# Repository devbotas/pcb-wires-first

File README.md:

# The Problem

Wireless IoT sucks.

It's unreliable and breaks all the time. There's not such thing as reliable, maintenance-free, wireless IoT.

If it runs on batteries - that's even worse.

Another problem - central IoT hubs. If those break, lose connection, decides to reboot ar whatever - my smart house immediatelly becomes non-functional.

# The Solution

Put the analog wires first! So that light switches continue to operate even if smart features decide to stop working.

# The Boards

## Gateway

This is a simple carrier board for WizNET W55RP20 development module. It cannot do much by itself - maybe blink some LEDs. Real functionality (and also power) should come from the JST PH headers.

Can be mounted on M or L size Holey board.

## Voltage converter

Takes 12-24V input (technically, 5-70V, but these voltages may not be supported on the other modules that this one is supposed to power) and creates 3.3V output so Gateway or other low power modules could be connected through the JST XH connector. Additionally, there are multiple JST VH connectors, which act as a power switch to connect multiple power hungry modules, like the Switcher.

Two can be mounted on a single Holey-S board.

## Switcher

Originally meant to control LED lights, but it can switch anything. It has one switchable 12/24V output (should be able to handle 4A). Output can be controlled simultaneously in multiple ways:

* ON wire: shorting this to GND for 100ms will turn the switch on.
* OFF wire: shorting this to GND for 100ms will turn the switch off.
* TGL wire: shorting this to GND for 100ms will toggle the switch.
* I2C directly: software based commands that can turn switch on or off and read the current state.

The idea here that ON/OFF/TGL signals could be wired to the physical wall switches directly, any smart features being entirely optional. So the switch will operate as a dumb-switch.

Renesas HVPAK SLG47115 chip serves both as a high-power switch and an input sanitizer. For example, if faulty hardware shorts ON signal to GND permanently, OFF and TGL signals continue to operate normally. 

Two can be mounted on a single Holey-S board.

## Holey boards

These are very handy to mount modules listed above, or maybe anything. They have a grid of 3.2mm diameter holes (hence the name) on a 5mm grid. They work perfectly with any M3 mounting hardware and come in the following sizes:

* L - 160x100 mm
* M - 100x80 mm
* S - 80x40 mm

So, one M board can fit exactly two S boards, and one L board can fit exactly 2 M boards. This allows some neat and functional arrangement.

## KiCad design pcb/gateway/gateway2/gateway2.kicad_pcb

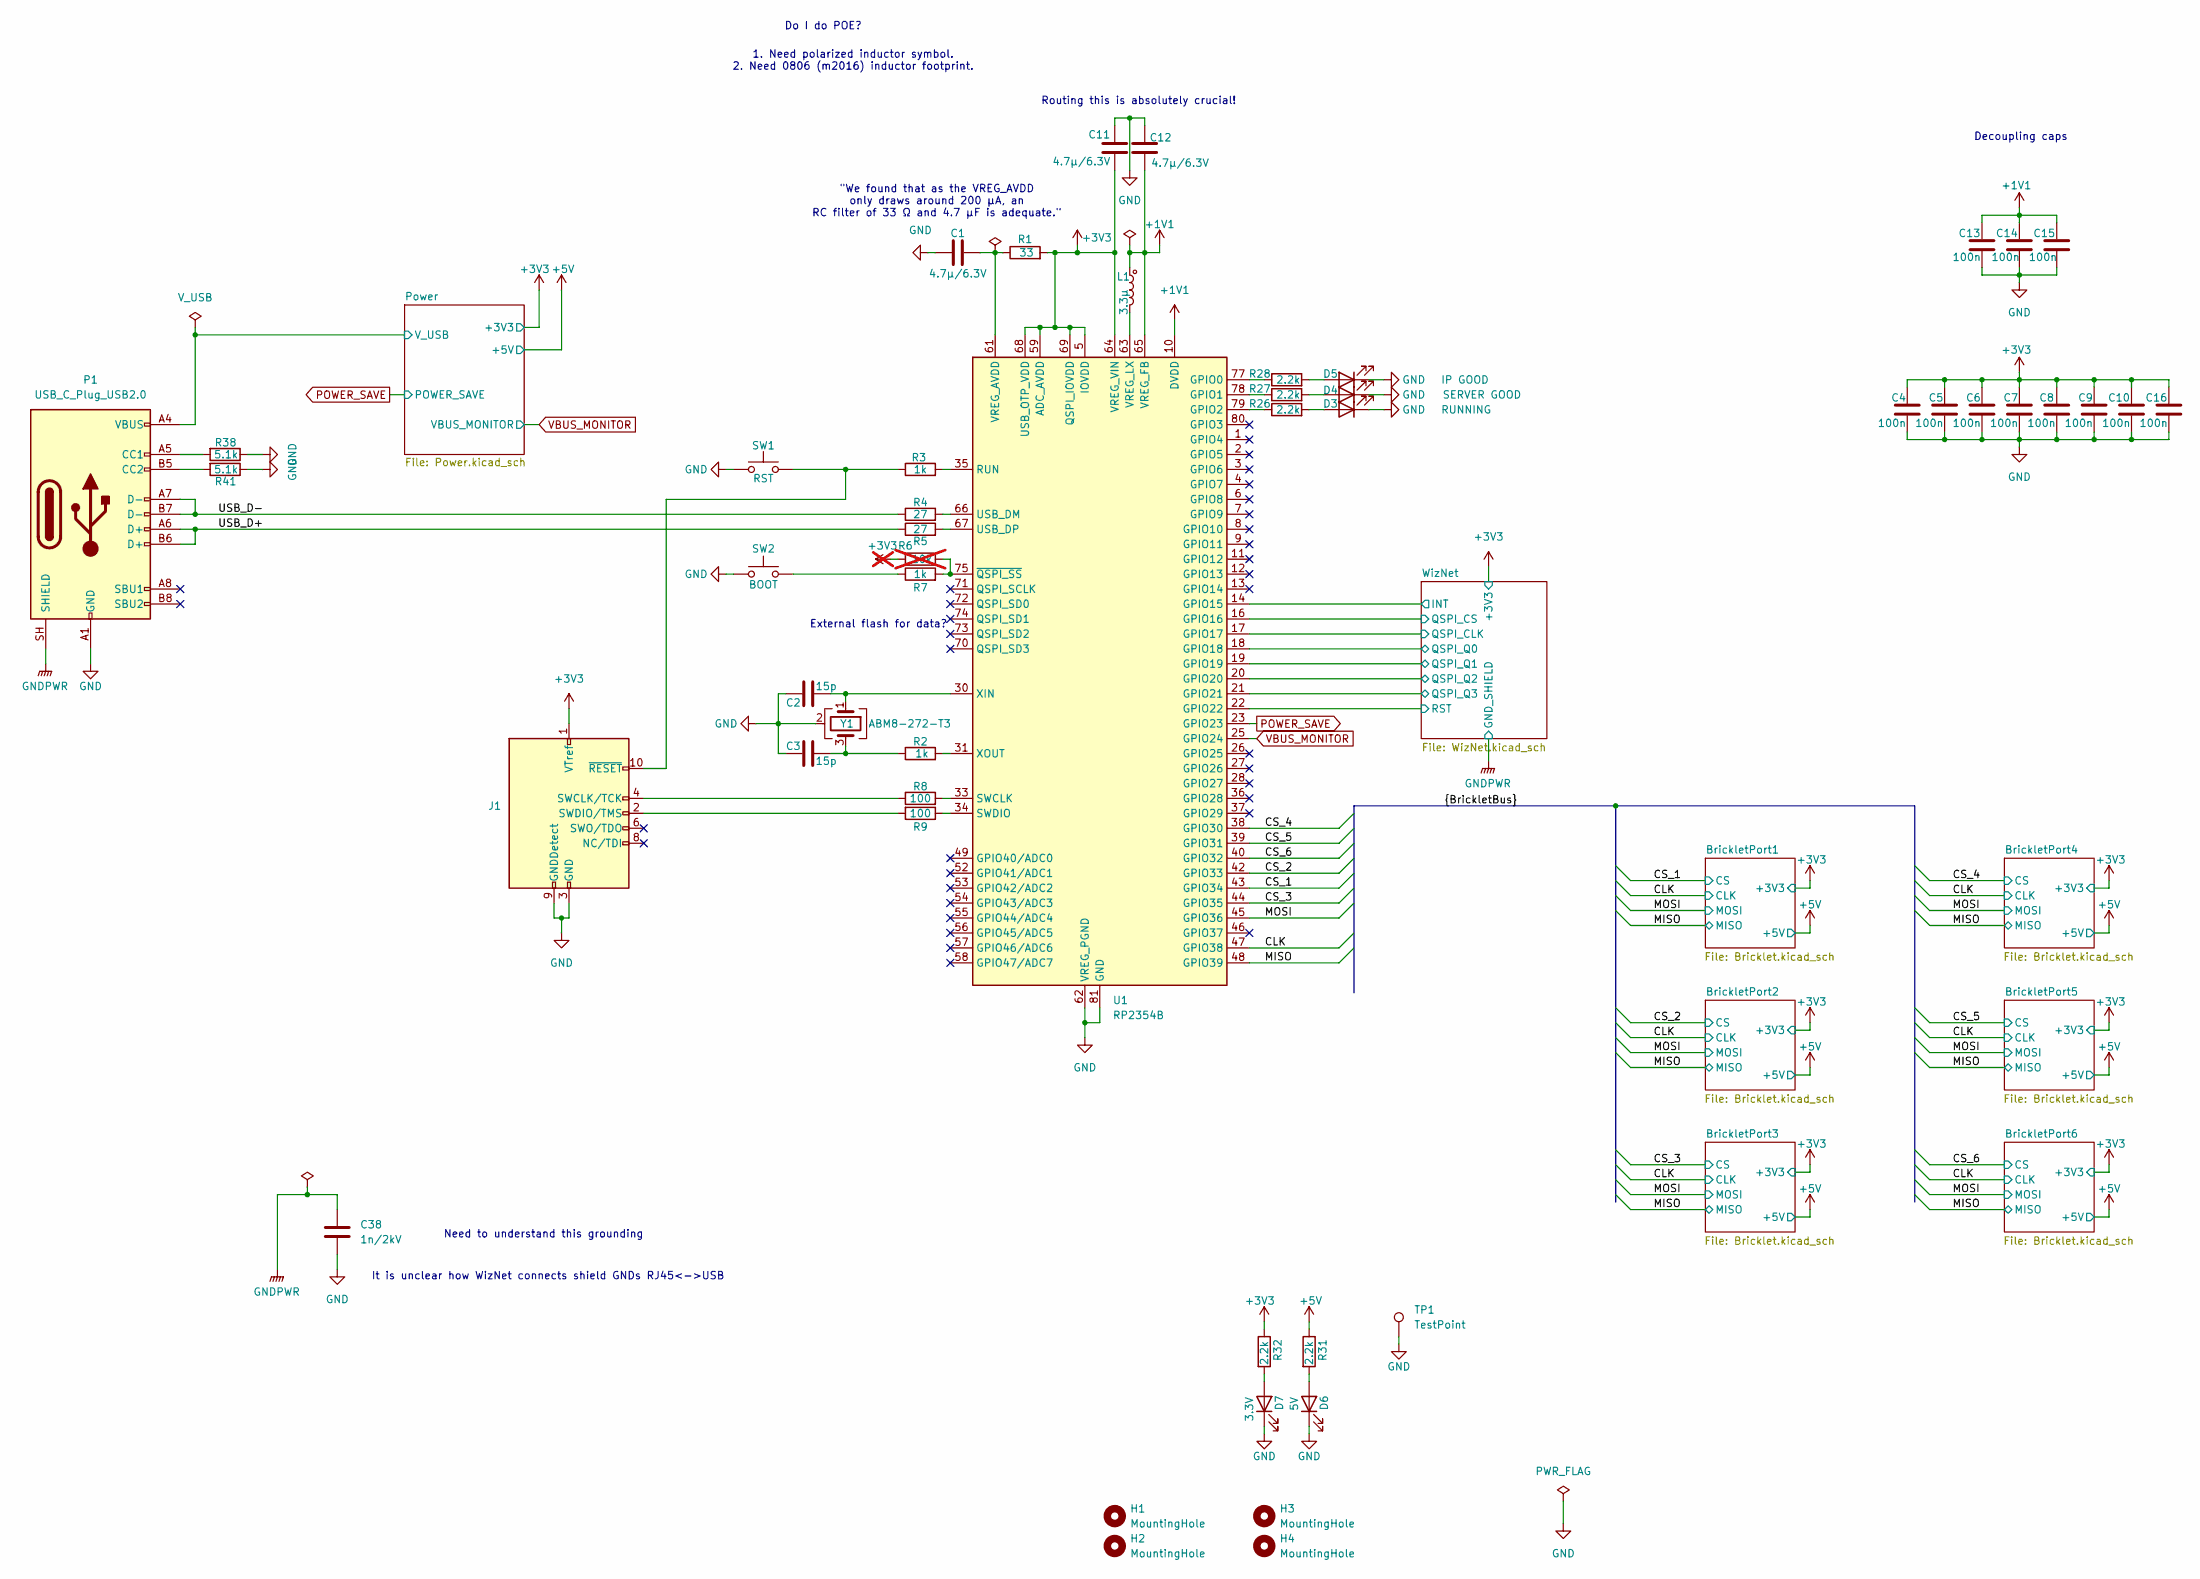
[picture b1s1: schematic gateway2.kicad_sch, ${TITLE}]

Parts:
C1, C11, C12: 4.7μ/6.3V; C_0603_1608Metric
C2, C3: 15p; C_0603_1608Metric
C4, C5, C6, C7, C8, C9, C10, C13, C14, C15, C16: 100n; C_0603_1608Metric
C38: 1n/2kV; C_0603_1608Metric
D3: RUNNING; D_0603_1608Metric
D4: SERVER GOOD; D_0603_1608Metric
D5: IP GOOD; D_0603_1608Metric
D6: 5V; D_0603_1608Metric
D7: 3.3V; D_0603_1608Metric
H1, H2, H3, H4: MountingHole; MountingHole_3.2mm_M3_NoCopper
J1: Conn_ARM_JTAG_SWD_10; PinHeader_2x05_P1.27mm_Vertical_SMD
L1: 3.3µ; L_Abracon_AOTA-B201610S
P1: USB_C_Plug_USB2.0; USB_C_Receptacle_GCT_USB4085
R1: 33; R_0603_1608Metric
R2, R3, R7: 1k; R_0603_1608Metric
R4, R5: 27; R_0603_1608Metric
R6: 10k; R_0603_1608Metric; not fitted
R8, R9: 100; R_0603_1608Metric
R26, R27, R28, R31, R32: 2.2k; R_0603_1608Metric
R38, R41: 5.1k; R_0603_1608Metric
SW1: RST; SW_SPST_CK_PTS815_Sx250SMTR_LFS
SW2: BOOT; SW_SPST_CK_PTS815_Sx250SMTR_LFS
TP1: TestPoint; TestPoint_Keystone_5019_Miniature
U1: RP2354B; QFN-80-1EP_10x10mm_P0.4mm_EP3.4x3.4mm
Y1: ABM8-272-T3; Crystal_SMD_Abracon_ABM8G-4Pin_3.2x2.5mm

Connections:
+1V1: C12.1, C13.2, C14.2, C15.2, L1.1, U1.10 (DVDD), U1.32 (DVDD), U1.51 (DVDD), U1.65 (VREG_FB)
+3V3: C4.2, C5.2, C6.2, C7.2, C8.2, C9.2, C10.2, C11.1, C16.2, J1.1 (VTref), R1.2, R6.1, R32.1, U1.5 (IOVDD), U1.15 (IOVDD), U1.24 (IOVDD), U1.29 (IOVDD), U1.41 (IOVDD), U1.50 (IOVDD), U1.59 (ADC_AVDD), U1.60 (IOVDD), U1.64 (VREG_VIN), U1.68 (USB_OTP_VDD), U1.69 (QSPI_IOVDD), U1.76 (IOVDD); also elsewhere on the board
+5V: R31.1; also elsewhere on the board
/CLK: U1.47 (GPIO38); also elsewhere on the board
/CS_1: U1.43 (GPIO34); also elsewhere on the board
/CS_2: U1.42 (GPIO33); also elsewhere on the board
/CS_3: U1.44 (GPIO35); also elsewhere on the board
/CS_4: U1.38 (GPIO30); also elsewhere on the board
/CS_5: U1.39 (GPIO31); also elsewhere on the board
/CS_6: U1.40 (GPIO32); also elsewhere on the board
/MISO: U1.48 (GPIO39); also elsewhere on the board
/MOSI: U1.45 (GPIO36); also elsewhere on the board
/Power/V_USB: P1.A4 (VBUS), P1.A9 (VBUS), P1.B4 (VBUS), P1.B9 (VBUS); also elsewhere on the board
/USB_D+: P1.A6 (D+), P1.B6 (D+), R5.1
/USB_D-: P1.A7 (D-), P1.B7 (D-), R4.1
/WizNet/INT: U1.14 (GPIO15); also elsewhere on the board
/WizNet/QSPI_CLK: U1.17 (GPIO17); also elsewhere on the board
/WizNet/QSPI_CS: U1.16 (GPIO16); also elsewhere on the board
/WizNet/QSPI_Q0: U1.18 (GPIO18); also elsewhere on the board
/WizNet/QSPI_Q1: U1.19 (GPIO19); also elsewhere on the board
/WizNet/QSPI_Q2: U1.20 (GPIO20); also elsewhere on the board
/WizNet/QSPI_Q3: U1.21 (GPIO21); also elsewhere on the board
/WizNet/RST: U1.22 (GPIO22); also elsewhere on the board
GND: C1.1, C2.1, C3.1, C4.1, C5.1, C6.1, C7.1, C8.1, C9.1, C10.1, C11.2, C12.2, C13.1, C14.1, C15.1, C16.1, C38.1, D3.1 (K), D4.1 (K), D5.1 (K), D6.1 (K), D7.1 (K), J1.3 (GND), J1.5 (GND), J1.9 (GNDDetect), P1.A1 (GND), P1.A12 (GND), P1.B1 (GND), P1.B12 (GND), R38.1, R41.1, SW1.1, SW2.1, TP1.1 (1_1), U1.62 (VREG_PGND), U1.81 (GND), Y1.2 (G), Y1.4 (G); also elsewhere on the board
GNDPWR: C38.2, P1.SH (SHIELD); also elsewhere on the board
unnamed: C3.2, R2.1, Y1.3
unnamed: D3.2 (A), R26.2
unnamed: D4.2 (A), R27.2
unnamed: D5.2 (A), R28.2
unnamed: D6.2 (A), R31.2
unnamed: D7.2 (A), R32.2
unnamed: J1.4 (SWCLK/TCK), R8.1
unnamed: J1.2 (SWDIO/TMS), R9.2
unnamed: J1.10 (~RESET), R3.1, SW1.2
unnamed: P1.A5 (CC1), R38.2
unnamed: P1.B5 (CC2), R41.2
unnamed: R7.1, SW2.2
unnamed: R28.1, U1.77 (GPIO0)
unnamed: R27.1, U1.78 (GPIO1)
unnamed: R26.1, U1.79 (GPIO2)
unnamed: R3.2, U1.35 (RUN)
unnamed: R8.2, U1.33 (SWCLK)
unnamed: R9.1, U1.34 (SWDIO)
unnamed: R4.2, U1.66 (USB_DM)
unnamed: R5.2, U1.67 (USB_DP)
unnamed: C1.2, R1.1, U1.61 (VREG_AVDD)
unnamed: L1.2, U1.63 (VREG_LX)
unnamed: C2.2, U1.30 (XIN), Y1.1
unnamed: R2.2, U1.31 (XOUT)
unnamed: R6.2, R7.2, U1.75 (~QSPI_SS)
POWER_SAVE: U1.23 (GPIO23); also elsewhere on the board
VBUS_MONITOR: U1.25 (GPIO24); also elsewhere on the board

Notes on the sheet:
Decoupling caps
Routing this is absolutely crucial!
Need to understand this grounding
1. Need polarized inductor symbol. 2. Need 0806 (m2016) inductor footprint.
It is unclear how WizNet connects shield GNDs RJ45<->USB
External flash for data?
Do I do POE?
"We found that as the VREG_AVDD only draws around 200 μA, an RC filter of 33 Ω and 4.7 μF is adequate."

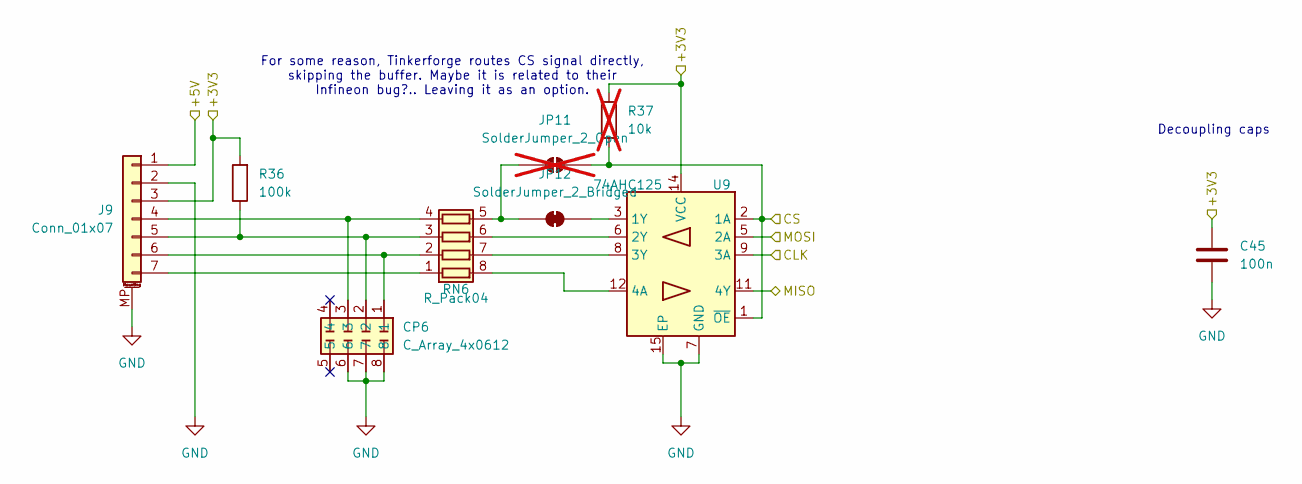
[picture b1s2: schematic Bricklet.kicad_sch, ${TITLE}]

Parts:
C45: 100n; C_0603_1608Metric
CP6: C_Array_4x0612
J9: Conn_01x07; JST_GH_BM07B-GHS-TBT_1x07-1MP_P1.25mm_Vertical
JP11: SolderJumper_2_Open; SolderJumper-2_P1.3mm_Open_RoundedPad1.0x1.5mm; not fitted
JP12: SolderJumper_2_Bridged; SolderJumper-2_P1.3mm_Bridged_RoundedPad1.0x1.5mm
R36: 100k; R_0603_1608Metric
R37: 10k; R_0603_1608Metric; not fitted
RN6: R_Pack04; R_Array_Concave_4x0603
U9: 74AHC125; DHVQFN-14-1EP_2.5x3mm_P0.5mm_EP1x1.5mm

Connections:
+3V3: C45.2, J9.3, R36.2, R37.2, U9.14 (VCC); also elsewhere on the board
+5V: J9.1; also elsewhere on the board
/CLK: U9.9 (3A); also elsewhere on the board
/CS_1: JP11.1 (A), R37.1, U9.1 (~OE), U9.2 (1A), U9.4 (~OE), U9.10 (~OE), U9.13 (~OE); also elsewhere on the board
/MISO: U9.11 (4Y); also elsewhere on the board
/MOSI: U9.5 (2A); also elsewhere on the board
GND: C45.1, CP6.6, CP6.7, CP6.8, J9.2, J9.MP (MountPin), U9.7 (GND), U9.15 (EP); also elsewhere on the board
unnamed: CP6.3, J9.4, RN6.4 (R4.1)
unnamed: CP6.2, J9.5, R36.1, RN6.3 (R3.1)
unnamed: CP6.1, J9.6, RN6.2 (R2.1)
unnamed: J9.7, RN6.1 (R1.1)
unnamed: JP11.2 (B), JP12.1 (A), RN6.5 (R4.2)
unnamed: JP12.2 (B), U9.3 (1Y)
unnamed: RN6.8 (R1.2), U9.12 (4A)
unnamed: RN6.7 (R2.2), U9.8 (3Y)
unnamed: RN6.6 (R3.2), U9.6 (2Y)

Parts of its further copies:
C42, C46, C47, C48, C49: 100n; C_0603_1608Metric
CP5, CP7, CP8, CP9, CP10: C_Array_4x0612
J8, J10, J11, J12, J13: Conn_01x07; JST_GH_BM07B-GHS-TBT_1x07-1MP_P1.25mm_Vertical
JP9, JP13, JP15, JP17, JP19: SolderJumper_2_Open; SolderJumper-2_P1.3mm_Open_RoundedPad1.0x1.5mm; not fitted
JP10, JP14, JP16, JP18, JP20: SolderJumper_2_Bridged; SolderJumper-2_P1.3mm_Bridged_RoundedPad1.0x1.5mm
R34, R39, R42, R44, R46: 100k; R_0603_1608Metric
R35, R40, R43, R45, R47: 10k; R_0603_1608Metric; not fitted
RN5, RN7, RN8, RN9, RN10: R_Pack04; R_Array_Concave_4x0603
U8, U10, U11, U12, U13: 74AHC125; DHVQFN-14-1EP_2.5x3mm_P0.5mm_EP1x1.5mm

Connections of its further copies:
+3V3: C42.2, C46.2, C47.2, C48.2, C49.2, J8.3, J10.3, J11.3, J12.3, J13.3, R34.2, R35.2, R39.2, R40.2, R42.2, R43.2, R44.2, R45.2, R46.2, R47.2, U8.14 (VCC), U10.14 (VCC), U11.14 (VCC), U12.14 (VCC), U13.14 (VCC); also elsewhere on the board
+5V: J8.1, J10.1, J11.1, J12.1, J13.1; also elsewhere on the board
/CLK: U8.9 (3A), U10.9 (3A), U11.9 (3A), U12.9 (3A), U13.9 (3A); also elsewhere on the board
/CS_2: JP9.1 (A), R35.1, U8.1 (~OE), U8.2 (1A), U8.4 (~OE), U8.10 (~OE), U8.13 (~OE); also elsewhere on the board
/CS_3: JP13.1 (A), R40.1, U10.1 (~OE), U10.2 (1A), U10.4 (~OE), U10.10 (~OE), U10.13 (~OE); also elsewhere on the board
/CS_4: JP15.1 (A), R43.1, U11.1 (~OE), U11.2 (1A), U11.4 (~OE), U11.10 (~OE), U11.13 (~OE); also elsewhere on the board
/CS_5: JP17.1 (A), R45.1, U12.1 (~OE), U12.2 (1A), U12.4 (~OE), U12.10 (~OE), U12.13 (~OE); also elsewhere on the board
/CS_6: JP19.1 (A), R47.1, U13.1 (~OE), U13.2 (1A), U13.4 (~OE), U13.10 (~OE), U13.13 (~OE); also elsewhere on the board
/MISO: U8.11 (4Y), U10.11 (4Y), U11.11 (4Y), U12.11 (4Y), U13.11 (4Y); also elsewhere on the board
/MOSI: U8.5 (2A), U10.5 (2A), U11.5 (2A), U12.5 (2A), U13.5 (2A); also elsewhere on the board
GND: C42.1, C46.1, C47.1, C48.1, C49.1, CP5.6, CP5.7, CP5.8, CP7.6, CP7.7, CP7.8, CP8.6, CP8.7, CP8.8, CP9.6, CP9.7, CP9.8, CP10.6, CP10.7, CP10.8, J8.2, J8.MP (MountPin), J10.2, J10.MP (MountPin), J11.2, J11.MP (MountPin), J12.2, J12.MP (MountPin), J13.2, J13.MP (MountPin), U8.7 (GND), U8.15 (EP), U10.7 (GND), U10.15 (EP), U11.7 (GND), U11.15 (EP), U12.7 (GND), U12.15 (EP), U13.7 (GND), U13.15 (EP); also elsewhere on the board
unnamed: CP5.3, J8.4, RN5.4 (R4.1)
unnamed: CP5.2, J8.5, R34.1, RN5.3 (R3.1)
unnamed: CP5.1, J8.6, RN5.2 (R2.1)
unnamed: J8.7, RN5.1 (R1.1)
unnamed: CP7.3, J10.4, RN7.4 (R4.1)
unnamed: CP7.2, J10.5, R39.1, RN7.3 (R3.1)
unnamed: CP7.1, J10.6, RN7.2 (R2.1)
unnamed: J10.7, RN7.1 (R1.1)
unnamed: CP8.3, J11.4, RN8.4 (R4.1)
unnamed: CP8.2, J11.5, R42.1, RN8.3 (R3.1)
unnamed: CP8.1, J11.6, RN8.2 (R2.1)
unnamed: J11.7, RN8.1 (R1.1)
unnamed: CP9.3, J12.4, RN9.4 (R4.1)
unnamed: CP9.2, J12.5, R44.1, RN9.3 (R3.1)
unnamed: CP9.1, J12.6, RN9.2 (R2.1)
unnamed: J12.7, RN9.1 (R1.1)
unnamed: CP10.3, J13.4, RN10.4 (R4.1)
unnamed: CP10.2, J13.5, R46.1, RN10.3 (R3.1)
unnamed: CP10.1, J13.6, RN10.2 (R2.1)
unnamed: J13.7, RN10.1 (R1.1)
unnamed: JP9.2 (B), JP10.1 (A), RN5.5 (R4.2)
unnamed: JP10.2 (B), U8.3 (1Y)
unnamed: JP13.2 (B), JP14.1 (A), RN7.5 (R4.2)
unnamed: JP14.2 (B), U10.3 (1Y)
unnamed: JP15.2 (B), JP16.1 (A), RN8.5 (R4.2)
unnamed: JP16.2 (B), U11.3 (1Y)
unnamed: JP17.2 (B), JP18.1 (A), RN9.5 (R4.2)
unnamed: JP18.2 (B), U12.3 (1Y)
unnamed: JP19.2 (B), JP20.1 (A), RN10.5 (R4.2)
unnamed: JP20.2 (B), U13.3 (1Y)
unnamed: RN5.8 (R1.2), U8.12 (4A)
unnamed: RN5.7 (R2.2), U8.8 (3Y)
unnamed: RN5.6 (R3.2), U8.6 (2Y)
unnamed: RN7.8 (R1.2), U10.12 (4A)
unnamed: RN7.7 (R2.2), U10.8 (3Y)
unnamed: RN7.6 (R3.2), U10.6 (2Y)
unnamed: RN8.8 (R1.2), U11.12 (4A)
unnamed: RN8.7 (R2.2), U11.8 (3Y)
unnamed: RN8.6 (R3.2), U11.6 (2Y)
unnamed: RN9.8 (R1.2), U12.12 (4A)
unnamed: RN9.7 (R2.2), U12.8 (3Y)
unnamed: RN9.6 (R3.2), U12.6 (2Y)
unnamed: RN10.8 (R1.2), U13.12 (4A)
unnamed: RN10.7 (R2.2), U13.8 (3Y)
unnamed: RN10.6 (R3.2), U13.6 (2Y)

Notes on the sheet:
For some reason, Tinkerforge routes CS signal directly, skipping the buffer. Maybe it is related to their Infineon bug?.. Leaving it as an option.
Decoupling caps

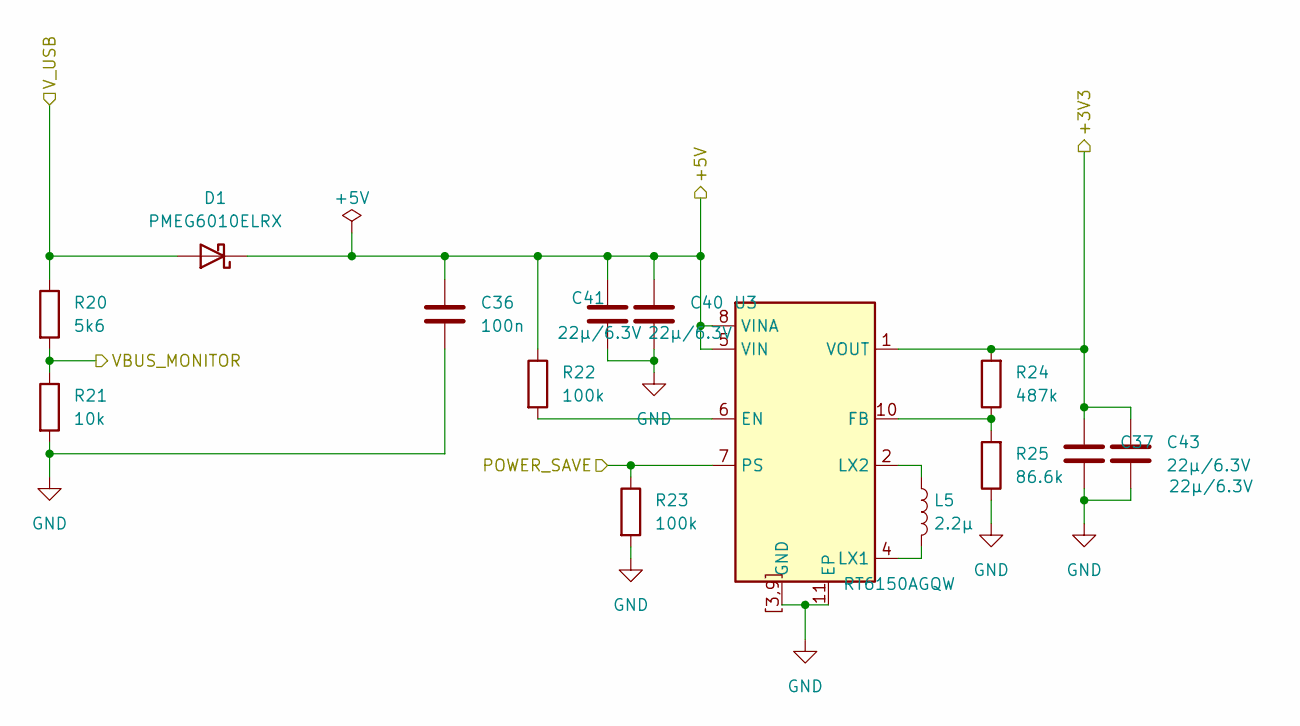
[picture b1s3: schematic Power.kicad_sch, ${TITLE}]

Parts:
C36: 100n; C_0603_1608Metric
C37, C40, C41, C43: 22μ/6.3V; C_1206_3216Metric
D1: PMEG6010ELRX; Nexperia_CFP3_SOD-123W
L5: 2.2μ; L_1206_3216Metric
R20: 5k6; R_0603_1608Metric
R21: 10k; R_0603_1608Metric
R22, R23: 100k; R_0603_1608Metric
R24: 487k; R_0603_1608Metric
R25: 86.6k; R_0603_1608Metric
U3: RT6150AGQW; WDFN-10-1EP_3x3mm_P0.5mm_EP1.8x2.5mm

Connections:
+3V3: C37.2, C43.2, R24.2, U3.1 (VOUT); also elsewhere on the board
+5V: C36.2, C40.2, C41.2, D1.1 (K), R22.1, U3.5 (VIN), U3.8 (VINA); also elsewhere on the board
/Power/V_USB: D1.2 (A), R20.1; also elsewhere on the board
GND: C36.1, C37.1, C40.1, C41.1, C43.1, R21.2, R23.2, R25.1, U3.3 (GND), U3.9 (GND), U3.11 (EP), U3.[3,9] (GND); also elsewhere on the board
unnamed: R22.2, U3.6 (EN)
unnamed: R24.1, R25.2, U3.10 (FB)
unnamed: L5.2, U3.4 (LX1)
unnamed: L5.1, U3.2 (LX2)
POWER_SAVE: R23.1, U3.7 (PS); also elsewhere on the board
VBUS_MONITOR: R20.2, R21.1; also elsewhere on the board

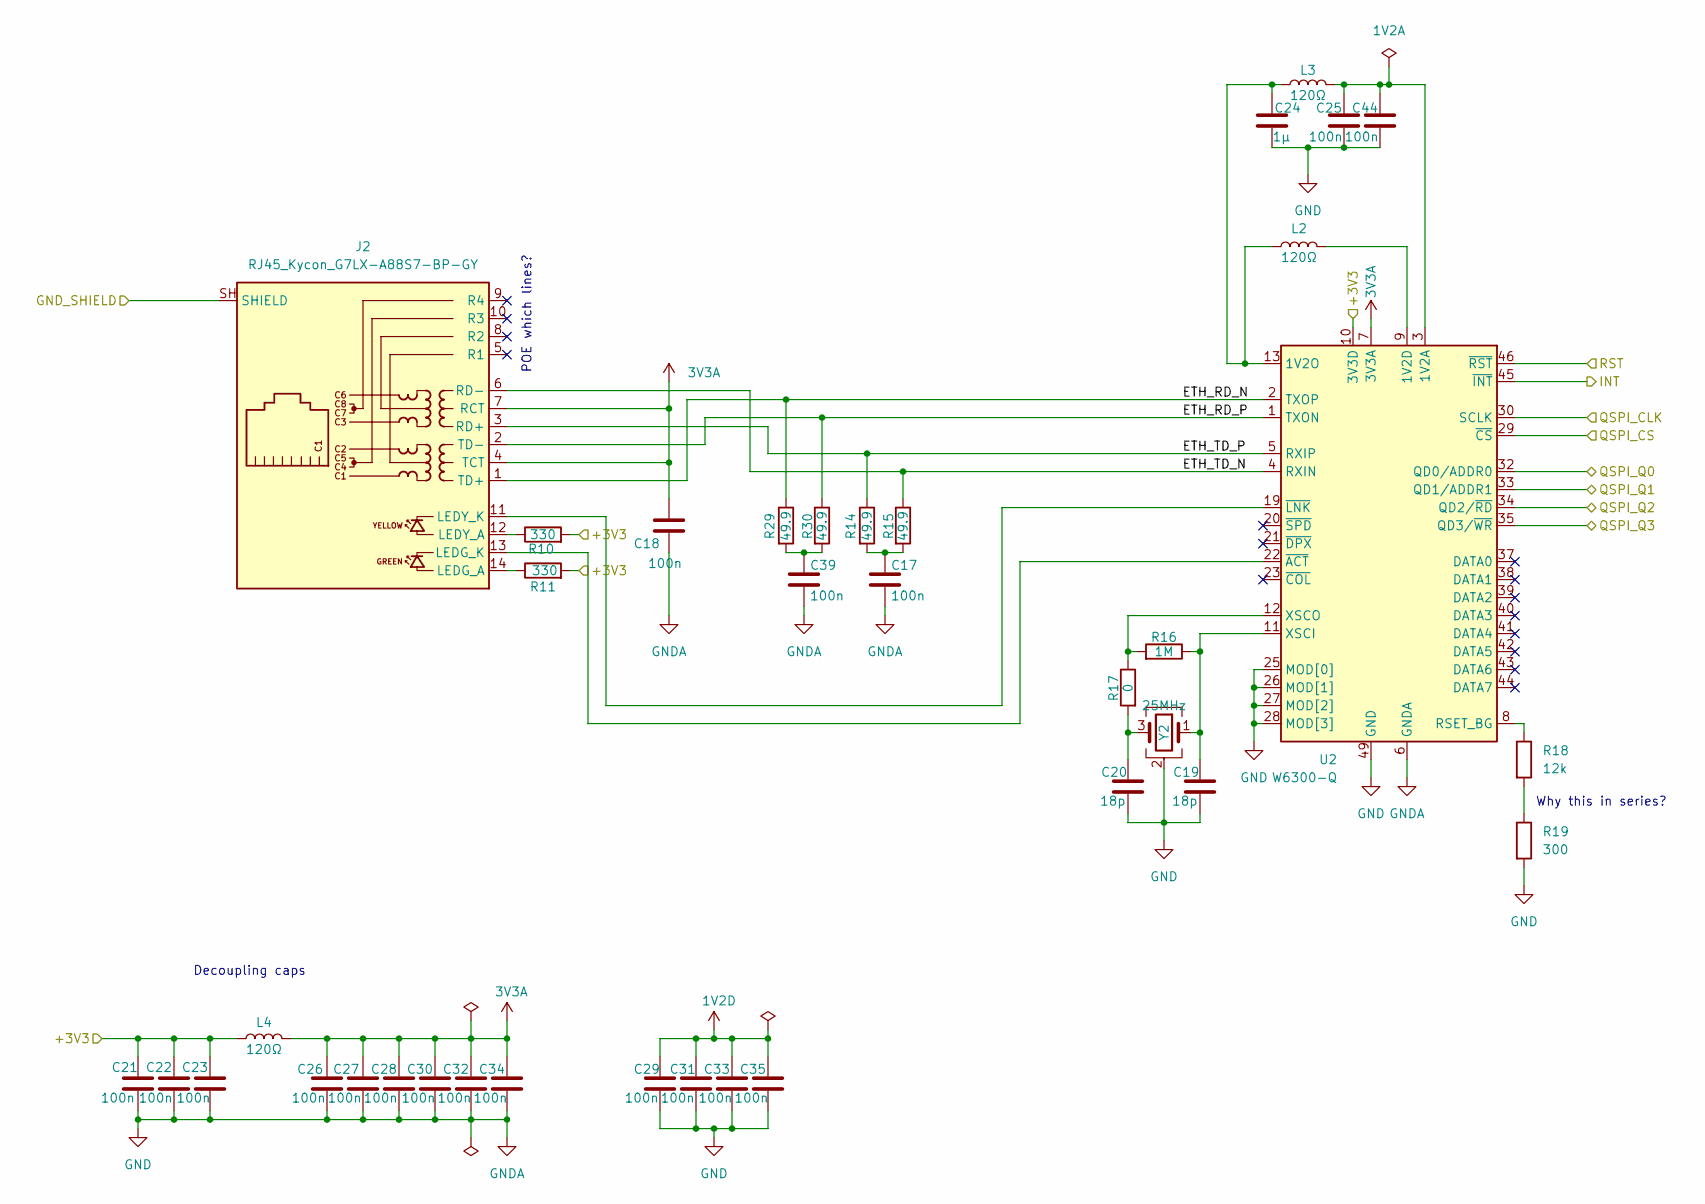
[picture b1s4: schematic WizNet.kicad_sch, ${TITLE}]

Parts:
C17, C18, C21, C22, C23, C25, C26, C27, C28, C29, C30, C31, C32, C33, C34, C35, C39, C44: 100n; C_0603_1608Metric
C19, C20: 18p; C_0603_1608Metric
C24: 1µ; C_0603_1608Metric
J2: RJ45_Kycon_G7LX-A88S7-BP-GY; RJ45_Kycon_G7LX-A88S7-BP-xx_Horizontal
L2, L3, L4: 120Ω; L_0603_1608Metric; MPN MPZ1608S121ATDH5
R10, R11: 330; R_0603_1608Metric
R14, R15, R29, R30: 49.9; R_0603_1608Metric
R16: 1M; R_0603_1608Metric
R17: 0; R_0603_1608Metric
R18: 12k; R_0603_1608Metric
R19: 300; R_0603_1608Metric
U2: W6300-Q; LQFP-48-1EP_7x7mm_P0.5mm_EP3.6x3.6mm
Y2: 25MHz; Crystal_SMD_Abracon_ABM8G-4Pin_3.2x2.5mm

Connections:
1V2A: C25.2, C44.2, L3.2, U2.3 (1V2A), U2.16 (1V2A)
3V3A: C18.2, C26.2, C27.2, C28.2, C30.2, C32.2, C34.2, J2.4 (TCT), J2.7 (RCT), L4.2, U2.7 (3V3A), U2.14 (3V3A)
+3V3: C21.2, C22.2, C23.2, L4.1, R10.2, R11.2, U2.10 (3V3D), U2.24 (3V3D), U2.36 (3V3D); also elsewhere on the board
/WizNet/ETH_RD_N: J2.1 (TD+), R29.1, U2.2 (TXOP)
/WizNet/ETH_RD_P: J2.2 (TD-), R30.1, U2.1 (TXON)
/WizNet/ETH_TD_N: J2.6 (RD-), R15.1, U2.4 (RXIN)
/WizNet/ETH_TD_P: J2.3 (RD+), R14.1, U2.5 (RXIP)
/WizNet/INT: U2.45 (~INT); also elsewhere on the board
/WizNet/QSPI_CLK: U2.30 (SCLK); also elsewhere on the board
/WizNet/QSPI_CS: U2.29 (~CS); also elsewhere on the board
/WizNet/QSPI_Q0: U2.32 (QD0/ADDR0); also elsewhere on the board
/WizNet/QSPI_Q1: U2.33 (QD1/ADDR1); also elsewhere on the board
/WizNet/QSPI_Q2: U2.34 (QD2/~RD); also elsewhere on the board
/WizNet/QSPI_Q3: U2.35 (QD3/~WR); also elsewhere on the board
/WizNet/RST: U2.46 (~RST); also elsewhere on the board
GND: C17.1, C18.1, C19.1, C20.1, C21.1, C22.1, C23.1, C24.1, C25.1, C26.1, C27.1, C28.1, C29.1, C30.1, C31.1, C32.1, C33.1, C34.1, C35.1, C39.1, C44.1, R19.2, U2.6 (GNDA), U2.15 (GNDA), U2.17 (GNDA), U2.25 (MOD[0]), U2.26 (MOD[1]), U2.27 (MOD[2]), U2.28 (MOD[3]), U2.48 (GNDA), U2.49 (GND), Y2.2 (G), Y2.4 (G); also elsewhere on the board
GNDPWR: J2.SH (SHIELD); also elsewhere on the board
unnamed: C17.2, R14.2, R15.2
unnamed: C20.2, R17.2, Y2.3
unnamed: C39.2, R29.2, R30.2
unnamed: J2.14 (LEDG_A), R11.1
unnamed: J2.13 (LEDG_K), U2.22 (~ACT)
unnamed: J2.12 (LEDY_A), R10.1
unnamed: J2.11 (LEDY_K), U2.19 (~LNK)
unnamed: R18.2, R19.1
unnamed: C24.2, L2.1, L3.1, U2.13 (1V2O)
unnamed: R18.1, U2.8 (RSET_BG)
unnamed: C19.2, R16.1, U2.11 (XSCI), Y2.1
unnamed: R16.2, R17.1, U2.12 (XSCO)

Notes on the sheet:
Decoupling caps
POE which lines?
Why this in series?

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
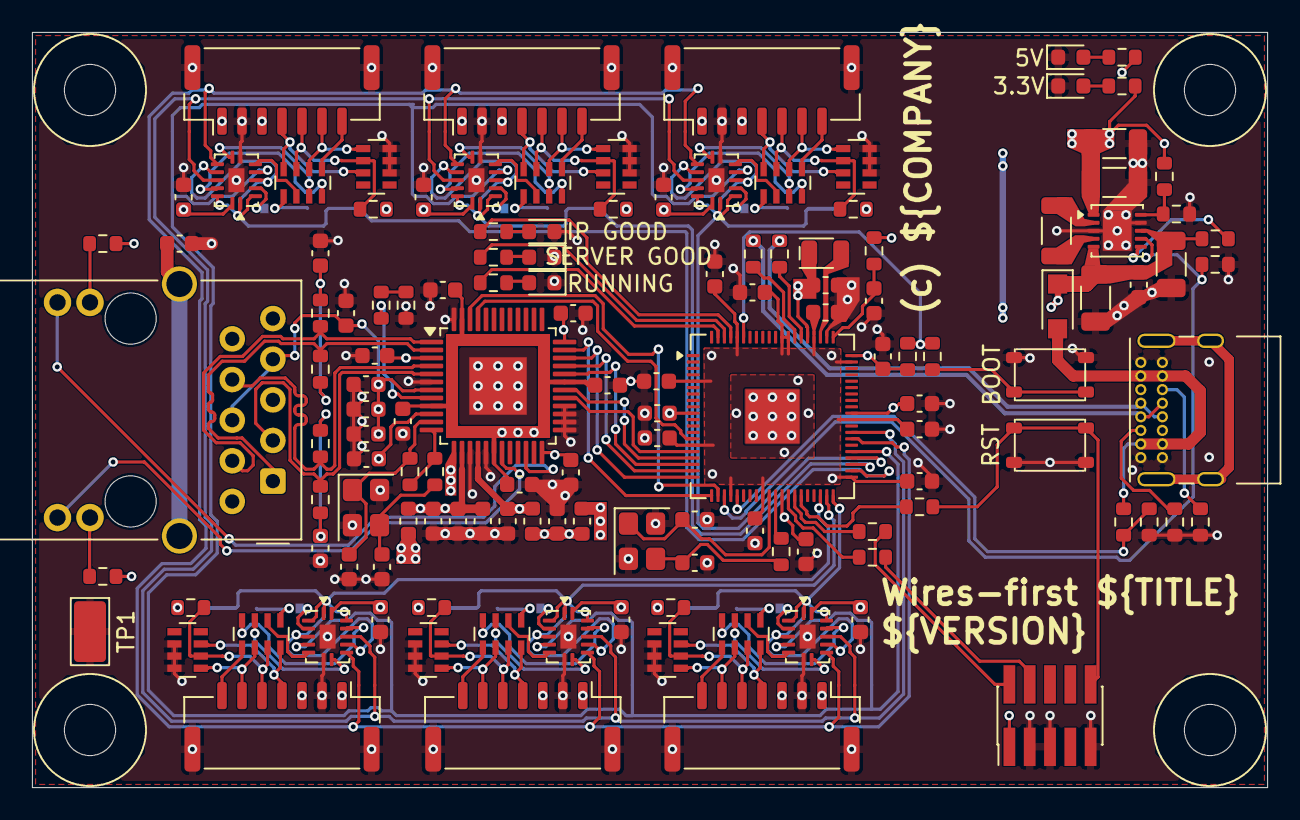
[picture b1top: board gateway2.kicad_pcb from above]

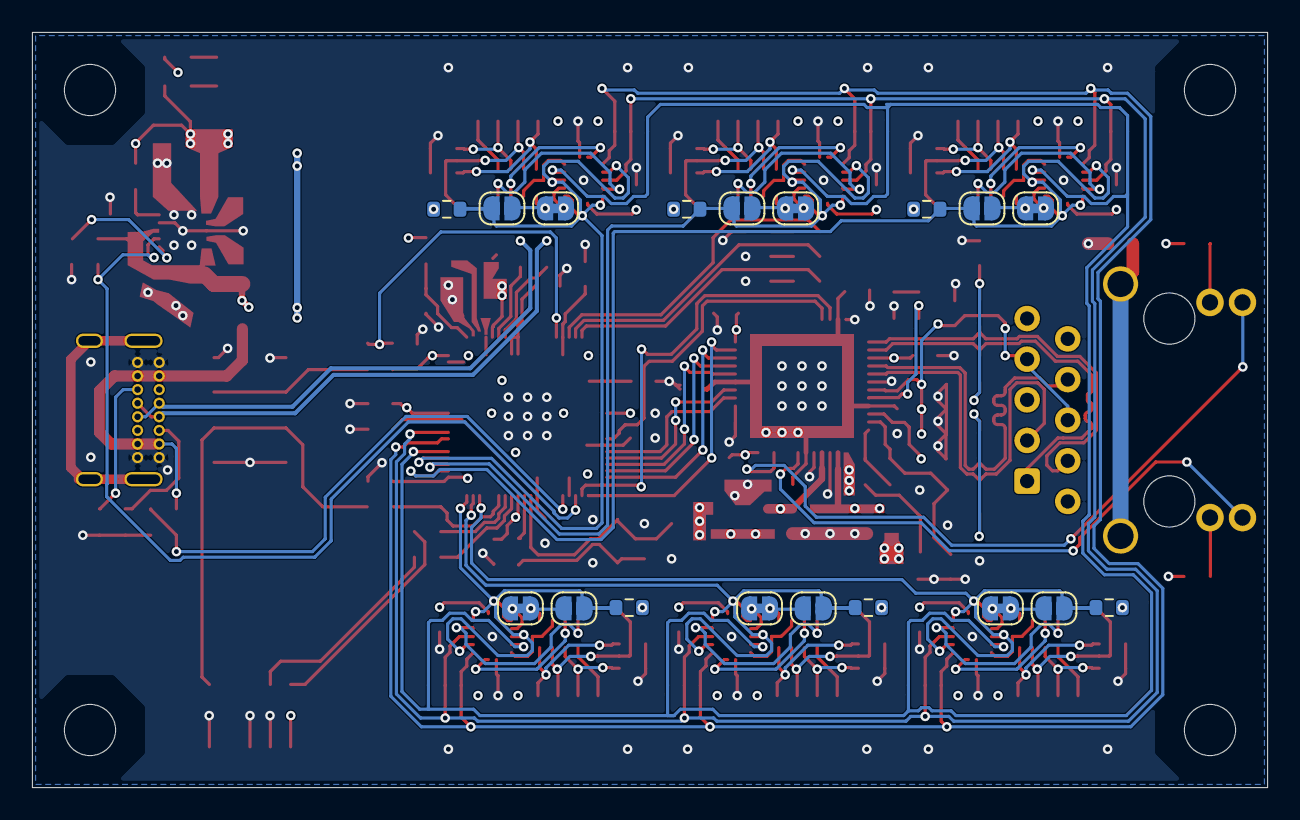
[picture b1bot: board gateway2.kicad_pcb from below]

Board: 4 copper layers, 77.2 x 47.2 mm, 155 parts (18 on the bottom side), 129 nets.

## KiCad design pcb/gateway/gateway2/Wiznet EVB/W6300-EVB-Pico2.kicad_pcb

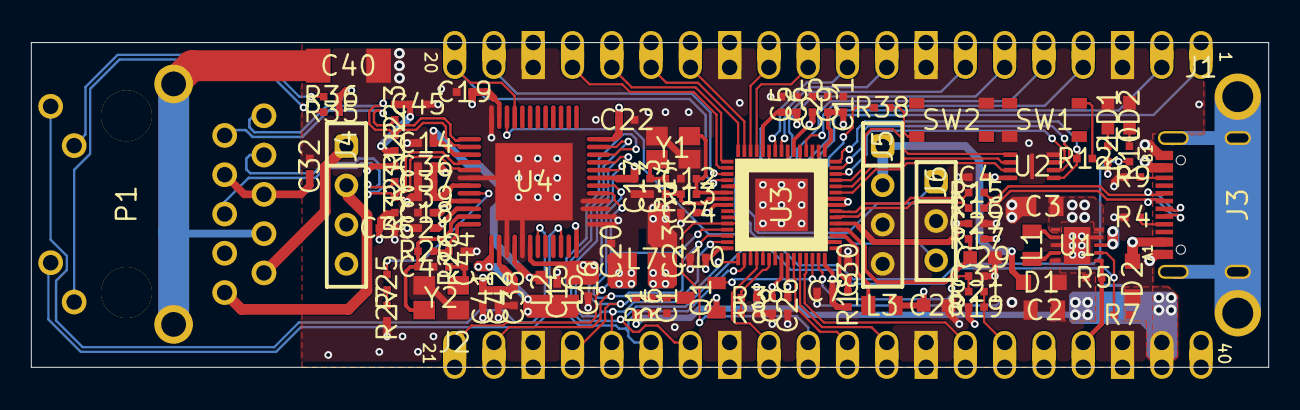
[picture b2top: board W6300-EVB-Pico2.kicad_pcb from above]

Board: 4 copper layers, 80.0 x 21.0 mm, 98 parts (0 on the bottom side), 89 nets.

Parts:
C1, C4, C6, C7, C8, C9, C10, C11, C14, C16, C17, C18, C19, C21, C22, C25, C26, C27, C32, C35, C36, C37, C39, C41, C42, C45: 0.1uF; CAP-0402
C2: 10u; CAP-0805
C3: 47u; CAP-0805
C5, C15, C20, C23, C24, C38: 1uF; CAP-0402
C12, C13: 15pF; CAP-0402
C28, C29: 10uF/1608; CAP-0603
C30, C31: 2u2; CAP-0402
C40: 1nF/2kV; CAP-1808
C43, C44: 18pF; CAP-0402
D1, D2: BAT60A; SOD-323(1-C,2-A)
J1, J2: 2.54mm 1x20 Pin Header DIP; IDC-1X20
J3: *; USB-TYPE-C-31-M-12
J4, J5: Header Socket 1x4_2.54mm; IDC-1X4(SOCKET)
J6: 2.54mm 1x3 Pin Header DIP; IDC-1X3
L1, L3: 2u2; IND-0805
L2, L6, L7: HH-1M1608-121JT; IND-0603
LD1: Green; LED-0603-RED
LD2: Green; LED-0603-GREEN
P1: TRJ4284AHNL; RB1-ZZ-0049
Q1: Q-2N7002; SOT23-3L
R1: 200K; RES-0402
R2, R10: 470R; RES-0402
R3: 5.6K; RES-0402
R4, R9: 5.1k; RES-0402
R5, R6, R7: 100K; RES-0402
R8: 10K; RES-0402
R12, R14, R38: 1K; RES-0402
R13: NC; RES-0402
R15, R16: 27R; RES-0402
R17, R26: 0R; RES-0402
R18: 10R; RES-0402
R19: 200R; RES-0402
R20: 1M; RES-0402
R21: 1R; RES-0402
R22, R23, R31, R32: 49.9R; RES-0402
R25: 12K/1%; RES-0402
R27: 300R; RES-0402
R35, R36: 330R; RES-0402
SW1, SW2: RKB2SJK250SMTR LFS; SW-RKB2
U1: SGM62112-3.3; SGM62112
U2: W25Q16JVUXIQ; SON50P300X200X60-9N
U3: RP2350-A; 7X7)
U4: W6300
Y1: 12MHz; OSC-TZ1067B
Y2: 25MHz; OSC-82J0626

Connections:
1V2A: C14.2, L2.1, U4.3, U4.16
1V2D: C16.2, C17.2, C18.2, C19.2, L6.2, U4.9, U4.18, U4.31, U4.47
1V2O: C15.2, L2.2, L6.1, U4.13
3V3: C3.2, C4.2, C5.2, C6.2, C7.2, C8.2, C9.2, C10.2, C11.2, C20.2, C21.2, C22.2, J2.16, L7.1, Q1.1, R2.1, R17.1, R18.1, R19.1, R35.2, R36.2, U1.1, U1.10, U2.8, U3.1, U3.11, U3.20, U3.30, U3.38, U3.45, U3.53, U3.54, U4.10, U4.24, U4.36
3V3A: C23.2, C32.2, C36.2, C37.2, C38.2, C39.2, C41.2, C42.2, L7.2, P1.R4, P1.R5, U4.7, U4.14
3V3_EN: J2.17, R5.2, U1.6
ACTn: P1.L2, U4.22
ADC_VREF: J2.15, R19.2, R21.2
CGND: C40.1, J3.S1, J3.S2, J3.S3, J3.S4, P1.R7, P1.S1, P1.S2
GPIO0: J1.1, U3.2
GPIO1: J1.2, U3.3
GPIO2: J1.4, U3.4
GPIO3: J1.5, U3.5
GPIO4: J1.6, U3.7
GPIO5: J1.7, U3.8
GPIO6: J1.9, U3.9
GPIO7: J1.10, U3.10
GPIO8: J1.11, U3.12
GPIO9: J1.12, U3.13
GPIO10: J1.14, U3.14
GPIO11: J1.15, U3.15
GPIO12: J1.16, U3.16
GPIO13: J1.17, U3.17
GPIO14: J1.19, U3.18
GPIO15: J1.20, U3.19, U4.45
GPIO16: J2.1, U3.27, U4.29
GPIO17: J2.2, U3.28, U4.30
GPIO18: J2.4, U3.29, U4.32
GPIO19: J2.5, U3.31, U4.33
GPIO20: J2.6, U3.32, U4.34
GPIO21: J2.7, U3.33, U4.35
GPIO22: J2.9, U3.34, U4.46
GPIO23: R7.2, U1.7, U3.35
GPIO24: R3.1, R8.2, U3.36
GPIO25: R10.2, U3.37
GPIO26/ADC0: J2.11, U3.40
GPIO27/ADC1: J2.12, U3.41
GPIO28/ADC2: J2.14, U3.42
GPIO29/ADC3: Q1.2, U3.43
LINKn: P1.L4, U4.19
NetC1_1: C1.1, Q1.3, R1.1, R6.2
NetC13_1: C13.1, R14.1, Y1.3
NetC31_2: C31.2, R21.1, U3.44
NetC35_2: C35.2, R31.1, R32.1
NetC43_2: C43.2, R20.1, U4.11, Y2.1
NetC44_2: C44.2, R26.1, Y2.3
NetC45_1: C45.1, R22.2, R23.2
NetJ3_A5: J3.A5, R4.1
NetJ3_B5: J3.B5, R9.2
NetL1_1: L1.1, U1.4
NetL1_2: L1.2, U1.2
NetLD1_1: LD1.1, R2.2
NetLD2_1: LD2.1, R10.1
NetP1_L1: P1.L1, R35.1
NetP1_L3: P1.L3, R36.1
NetP1_R1: P1.R1, R22.1, U4.2
NetP1_R2: P1.R2, R23.1, U4.1
NetP1_R3: P1.R3, R32.2, U4.5
NetP1_R6: P1.R6, R31.2, U4.4
NetR12_2: R12.2, SW1.2
NetR15_1: R15.1, U3.52
NetR16_1: R16.1, U3.51
NetR20_2: R20.2, R26.2, U4.12
NetR25_1: R25.1, U4.8
NetR25_2: R25.2, R27.1
NetR38_1: R38.1, SW2.2
POE: D1.2, J5.1, J5.2
QSPI_SCLK: U2.6, U3.56
QSPI_SD0: U2.5, U3.57
QSPI_SD1: U2.2, U3.59
QSPI_SD2: U2.3, U3.58
QSPI_SD3: U2.7, U3.55
QSPI_SS: R12.1, U2.1, U3.60
RUN: J2.10, R38.2, U3.26
SWCLK: J6.1, U3.24
SWDIO: J6.3, U3.25
USB_DM: J3.A7, J3.B7, R16.2
USB_DP: J3.A6, J3.B6, R15.2
VBUS: D2.2, J2.20, J3.A4_B9, J3.B4_A9
VC1: J4.1, P1.R9
VC2: J4.2, P1.R10
VREG_AVDD: C30.2, R18.2, U3.46
VREG_FB: C24.2, C25.2, C26.2, C27.2, C28.2, L3.2, U3.6, U3.23, U3.39, U3.50
VREG_LX: L3.1, U3.48
VREG_PGND: C1.2, C2.1, C3.1, C4.1, C5.1, C6.1, C7.1, C8.1, C9.1, C10.1, C11.1, C12.2, C13.2, C14.1, C15.1, C16.1, C17.1, C18.1, C19.1, C20.1, C21.1, C22.1, C23.1, C24.1, C25.1, C26.1, C27.1, C28.1, C29.1, C30.1, C31.1, C32.1, C35.1, C36.1, C37.1, C38.1, C39.1, C40.2, C41.1, C42.1, C43.1, C44.1, C45.2, J1.3, J1.8, J1.13, J1.18, J2.3, J2.8, J2.13, J2.18, J3.A1_B12, J3.B1_A12, J5.3, J5.4, J6.2, LD1.2, LD2.2, R4.2, R6.1, R8.1, R9.1, R27.2, SW1.3, SW2.3, U1.3, U1.9, U2.4, U2.9, U3.47, U3.61, U4.6, U4.15, U4.17, U4.25, U4.26, U4.27, U4.28, U4.48, U4.49, Y1.2, Y1.4, Y2.2, Y2.4
VREG_VIN: C29.2, R17.2, U3.49
VSYS: C2.2, D1.1, D2.1, J2.19, R1.2, R3.2, R5.1, R7.1, U1.5, U1.8
XIN: C12.1, R13.2, U3.21, Y1.1
XOUT: R13.1, R14.2, U3.22

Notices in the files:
pcb/pcb-wires-first.kicad_pcb:
Copyright (c) devbotas
